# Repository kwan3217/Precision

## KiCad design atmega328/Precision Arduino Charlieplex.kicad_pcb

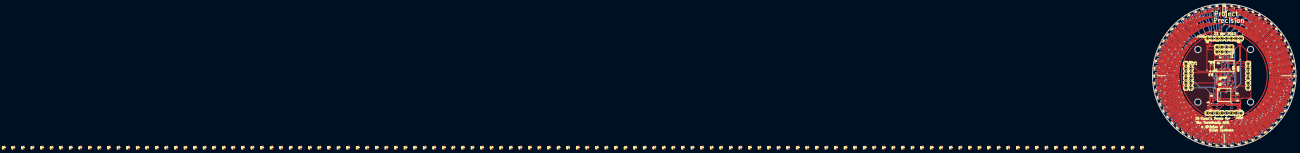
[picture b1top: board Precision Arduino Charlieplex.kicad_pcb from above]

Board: 2 copper layers, 76.2 x 76.2 mm, 272 parts (0 on the bottom side), 52 nets.

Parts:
C10, C418: 4.7uF; 0603-CAP
C407, C408: 18pF; 0603-CAP
C420, C502: 100nF; 0603-CAP
D0, D1, D2, D3, D4, D5, D6, D7, D8, D9, D10, D11, D12, D13, D14, D15, D16, D17, D18, D19, D20, D21, D22, D23, D24, D25, D26, D27, D28, D29, D30, D31, D32, D33, D34, D35, D36, D37, D38, D39, D40, D41, D42, D43, D44, D45, D46, D47, D48, D49, D50, D51, D52, D53, D54, D55, D56, D57, D58, D59, D502: RED; LED-0603
D100, D101, D102, D103, D104, D105, D106, D107, D108, D109, D110, D111, D112, D113, D114, D115, D116, D117, D118, D119, D120, D121, D122, D123, D124, D125, D126, D127, D128, D129, D130, D131, D132, D133, D134, D135, D136, D137, D138, D139, D140, D141, D142, D143, D144, D145, D146, D147, D148, D149, D150, D151, D152, D153, D154, D155, D156, D157, D158, D159: YELLOW; LED-0603
D200, D201, D202, D203, D204, D205, D206, D207, D208, D209, D210, D211, D212, D213, D214, D215, D216, D217, D218, D219, D220, D221, D222, D223, D224, D225, D226, D227, D228, D229, D230, D231, D232, D233, D234, D235, D236, D237, D238, D239, D240, D241, D242, D243, D244, D245, D246, D247, D248, D249, D250, D251, D252, D253, D254, D255, D256, D257, D258, D259: GREEN; LED-0603
D300, D301, D302, D303, D304, D305, D306, D307, D308, D309, D310, D311, D312, D313, D314, D315, D316, D317, D318, D319, D320, D321, D322, D323, D324, D325, D326, D327, D328, D329, D330, D331, D332, D333, D334, D335, D336, D337, D338, D339, D340, D341, D342, D343, D344, D345, D346, D347, D348, D349, D350, D351, D352, D353, D354, D355, D356, D357, D358, D359, D501: BLUE; LED-0603
J1, J2, J4: M04PTH; 1X04
J3, J5: M06SIP; 1X06
J405, J406: M081X08; 1X08
JP1, JP2, JP3, JP4: STAND-OFF
JP5: M02PTH; 1X02
R1, R2, R3, R4: 47; CRA04
R501, R502: 680; 0603-RES
R606: 10k; CRA04
S429: B3U-1100P
U401: ATMEGA328; TQFP32-08
U501: FT232RLSSOP; SSOP28DB
U602: ZF7; SC-70-6
Y401: 16MHz; CRYSTAL_SMD

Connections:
/3V3: J4.4, JP5.1, U501.17
/AT_RX: U401.30, U602.4
/AT_TX: J4.1, U401.31, U501.5
/D12: J3.5, J5.5, R606.8, U401.16, U602.6
/GPS_TX: J4.2, U602.3
/P01: J3.6, J5.6, R1.1, U401.15
/P02: R1.2, U401.2
/P03: R1.3, U401.14
/P04: R1.4, U401.13
/P05: R2.1, U401.12
/P06: R2.2, U401.11
/P07: R2.3, U401.10
/P08: R2.4, U401.9
/P09: R3.1, U401.1
/P10: R3.2, U401.28
/P11: R3.3, U401.27
/P12: R3.4, U401.26
/P13: R4.1, U401.25
/P14: R4.2, U401.24
/P15: R4.3, U401.23
/P16: J3.4, J5.4, R4.4, U401.17
/PPS: JP5.2, U401.32
/Q01: D0.C, D15.C, D29.C, D42.C, D54.C, D105.C, D115.C, D124.C, D132.C, D139.C, D145.C, D150.C, D154.C, D157.C, D159.C, J406.1, R1.8
/Q02: D0.A, D1.C, D16.C, D30.C, D43.C, D55.C, D106.C, D116.C, D125.C, D133.C, D140.C, D146.C, D151.C, D155.C, D158.C, J406.2, R1.7
/Q03: D1.A, D2.C, D15.A, D17.C, D31.C, D44.C, D56.C, D107.C, D117.C, D126.C, D134.C, D141.C, D147.C, D152.C, D156.C, J406.3, R1.6
/Q04: D2.A, D3.C, D16.A, D18.C, D29.A, D32.C, D45.C, D57.C, D108.C, D118.C, D127.C, D135.C, D142.C, D148.C, D153.C, J406.4, R1.5
/Q05: D3.A, D4.C, D17.A, D19.C, D30.A, D33.C, D42.A, D46.C, D58.C, D109.C, D119.C, D128.C, D136.C, D143.C, D149.C, J406.5, R2.8
/Q06: D4.A, D5.C, D18.A, D20.C, D31.A, D34.C, D43.A, D47.C, D54.A, D59.C, D110.C, D120.C, D129.C, D137.C, D144.C, J406.6, R2.7
/Q07: D5.A, D6.C, D19.A, D21.C, D32.A, D35.C, D44.A, D48.C, D55.A, D100.C, D105.A, D111.C, D121.C, D130.C, D138.C, J406.7, R2.6
/Q08: D6.A, D7.C, D20.A, D22.C, D33.A, D36.C, D45.A, D49.C, D56.A, D101.C, D106.A, D112.C, D115.A, D122.C, D131.C, J406.8, R2.5
/Q09: D7.A, D8.C, D21.A, D23.C, D34.A, D37.C, D46.A, D50.C, D57.A, D102.C, D107.A, D113.C, D116.A, D123.C, D124.A, J405.1, R3.8
/Q10: D8.A, D9.C, D22.A, D24.C, D35.A, D38.C, D47.A, D51.C, D58.A, D103.C, D108.A, D114.C, D117.A, D125.A, D132.A, J405.2, R3.7
/Q11: D9.A, D10.C, D23.A, D25.C, D36.A, D39.C, D48.A, D52.C, D59.A, D104.C, D109.A, D118.A, D126.A, D133.A, D139.A, J405.3, R3.6
/Q12: D10.A, D11.C, D24.A, D26.C, D37.A, D40.C, D49.A, D53.C, D100.A, D110.A, D119.A, D127.A, D134.A, D140.A, D145.A, J405.4, R3.5
/Q13: D11.A, D12.C, D25.A, D27.C, D38.A, D41.C, D50.A, D101.A, D111.A, D120.A, D128.A, D135.A, D141.A, D146.A, D150.A, J405.5, R4.8
/Q14: D12.A, D13.C, D26.A, D28.C, D39.A, D51.A, D102.A, D112.A, D121.A, D129.A, D136.A, D142.A, D147.A, D151.A, D154.A, J405.6, R4.7
/Q15: D13.A, D14.C, D27.A, D40.A, D52.A, D103.A, D113.A, D122.A, D130.A, D137.A, D143.A, D148.A, D152.A, D155.A, D157.A, J405.7, R4.6
/Q16: D14.A, D28.A, D41.A, D53.A, D104.A, D114.A, D123.A, D131.A, D138.A, D144.A, D149.A, D153.A, D156.A, D158.A, D159.A, J405.8, R4.5
/RESET: C502.1, J3.1, J5.1, R606.5, S429.P$2, U401.29
/USBD+: J1.1, J2.1, U501.15
/USBD-: J1.2, J2.2, U501.16
/USB_TX: U501.1, U602.1
/XTAL1: C407.2, U401.7, Y401.1
/XTAL2: C408.2, U401.8, Y401.3
GND: C10.2, C407.1, C408.1, C418.1, C420.2, J1.4, J2.4, J3.3, J4.3, J5.3, S429.P$1, S429.P$3, U401.3, U401.5, U401.21, U501.7, U501.18, U501.21, U501.25, U501.26, U602.2, Y401.2, Y401.4
unnamed: C420.1, U401.20
unnamed: C502.2, U501.2
unnamed: D501.C, R501.2
unnamed: D502.C, R502.2
unnamed: R501.1, U501.23
unnamed: R502.1, U501.22
VCC: C10.1, C418.2, D501.A, D502.A, J1.3, J2.3, J3.2, J5.2, R606.1, R606.4, U401.4, U401.6, U401.18, U501.4, U501.20, U602.5

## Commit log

2019-08-21 Adding Precision 2.0, the pure-Kicad, Python-routed next version of Project Precision
2019-08-21 Added Charlieplex traces. The bulk was done with CharlieplexTraces.py, with quite a bit of hand-optimization afterwards
2019-08-21 Removed Precision1.1 stuff from this folder
2019-08-21 Removed pycache from git
2019-08-21 Removed kicad cache stuff
2019-08-21 Finished connecting all signals, added buttons for setting time
2019-08-23 Moved manual set buttons to the GPS TX/RX lines
2021-09-29 Create LICENSE
2021-09-29 Renamed to match hardware
2021-09-30 Updated references to match refactoring
2021-09-30 Adding Precision 1.0 as built
2021-09-30 Updated to Precision 1.1 (the operational version)
2021-09-30 Updated permissions
